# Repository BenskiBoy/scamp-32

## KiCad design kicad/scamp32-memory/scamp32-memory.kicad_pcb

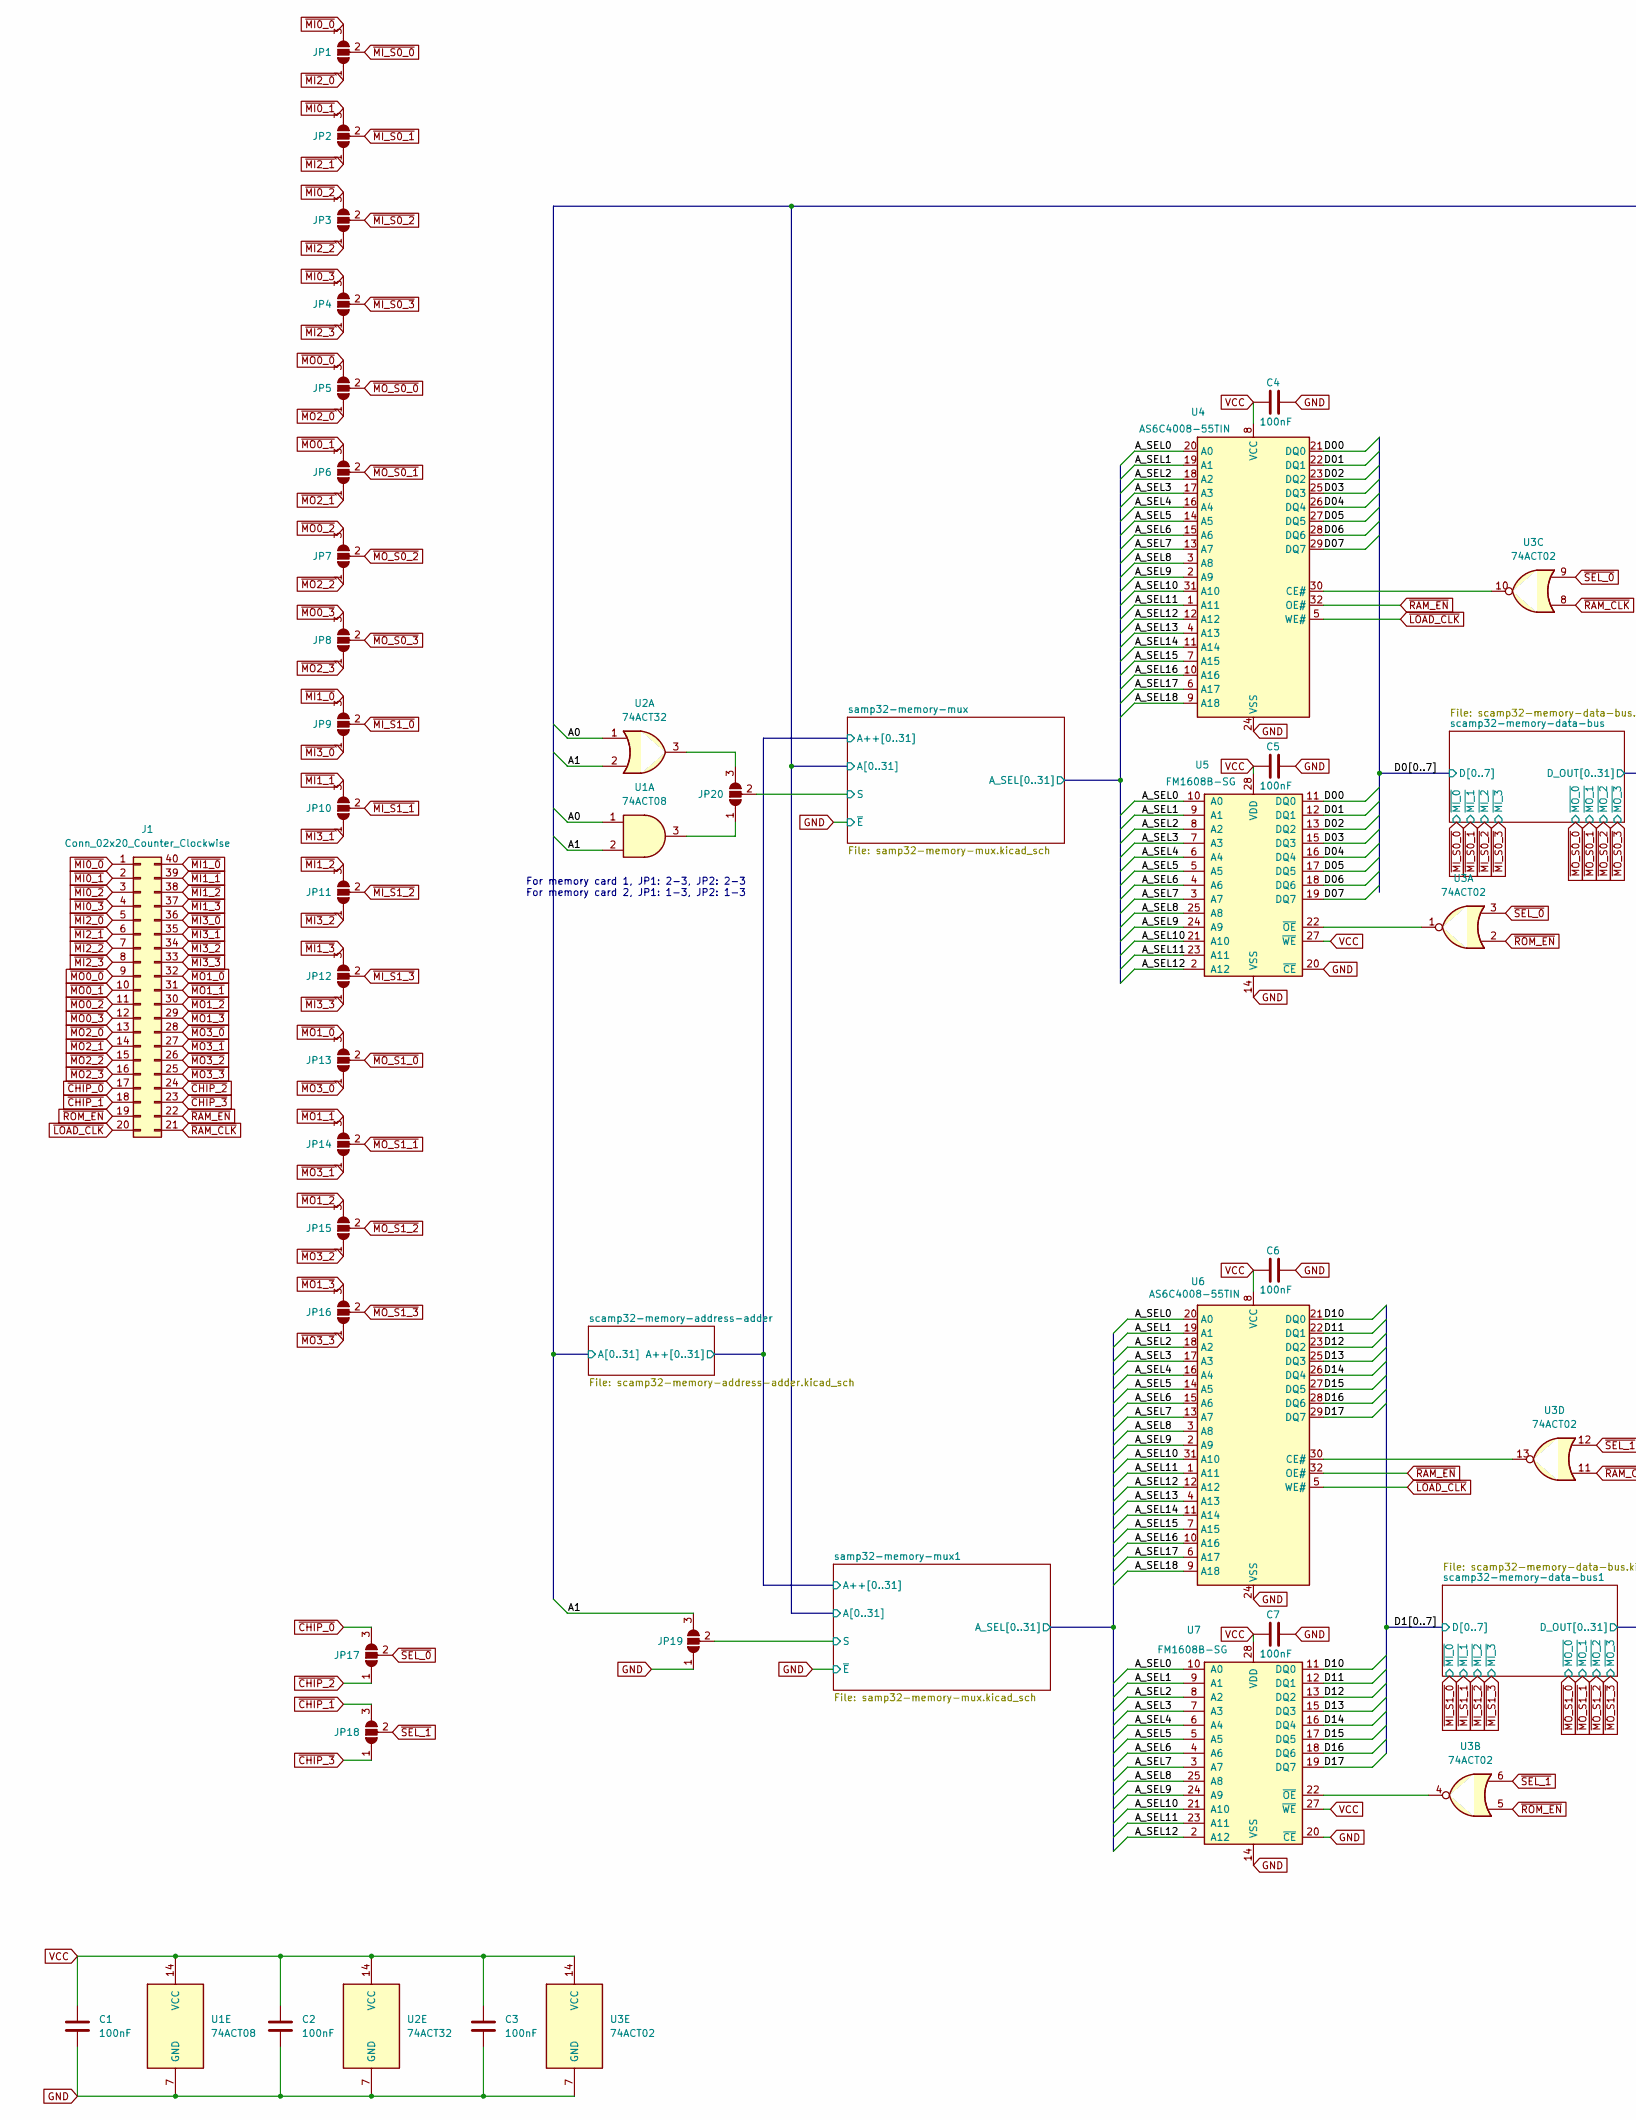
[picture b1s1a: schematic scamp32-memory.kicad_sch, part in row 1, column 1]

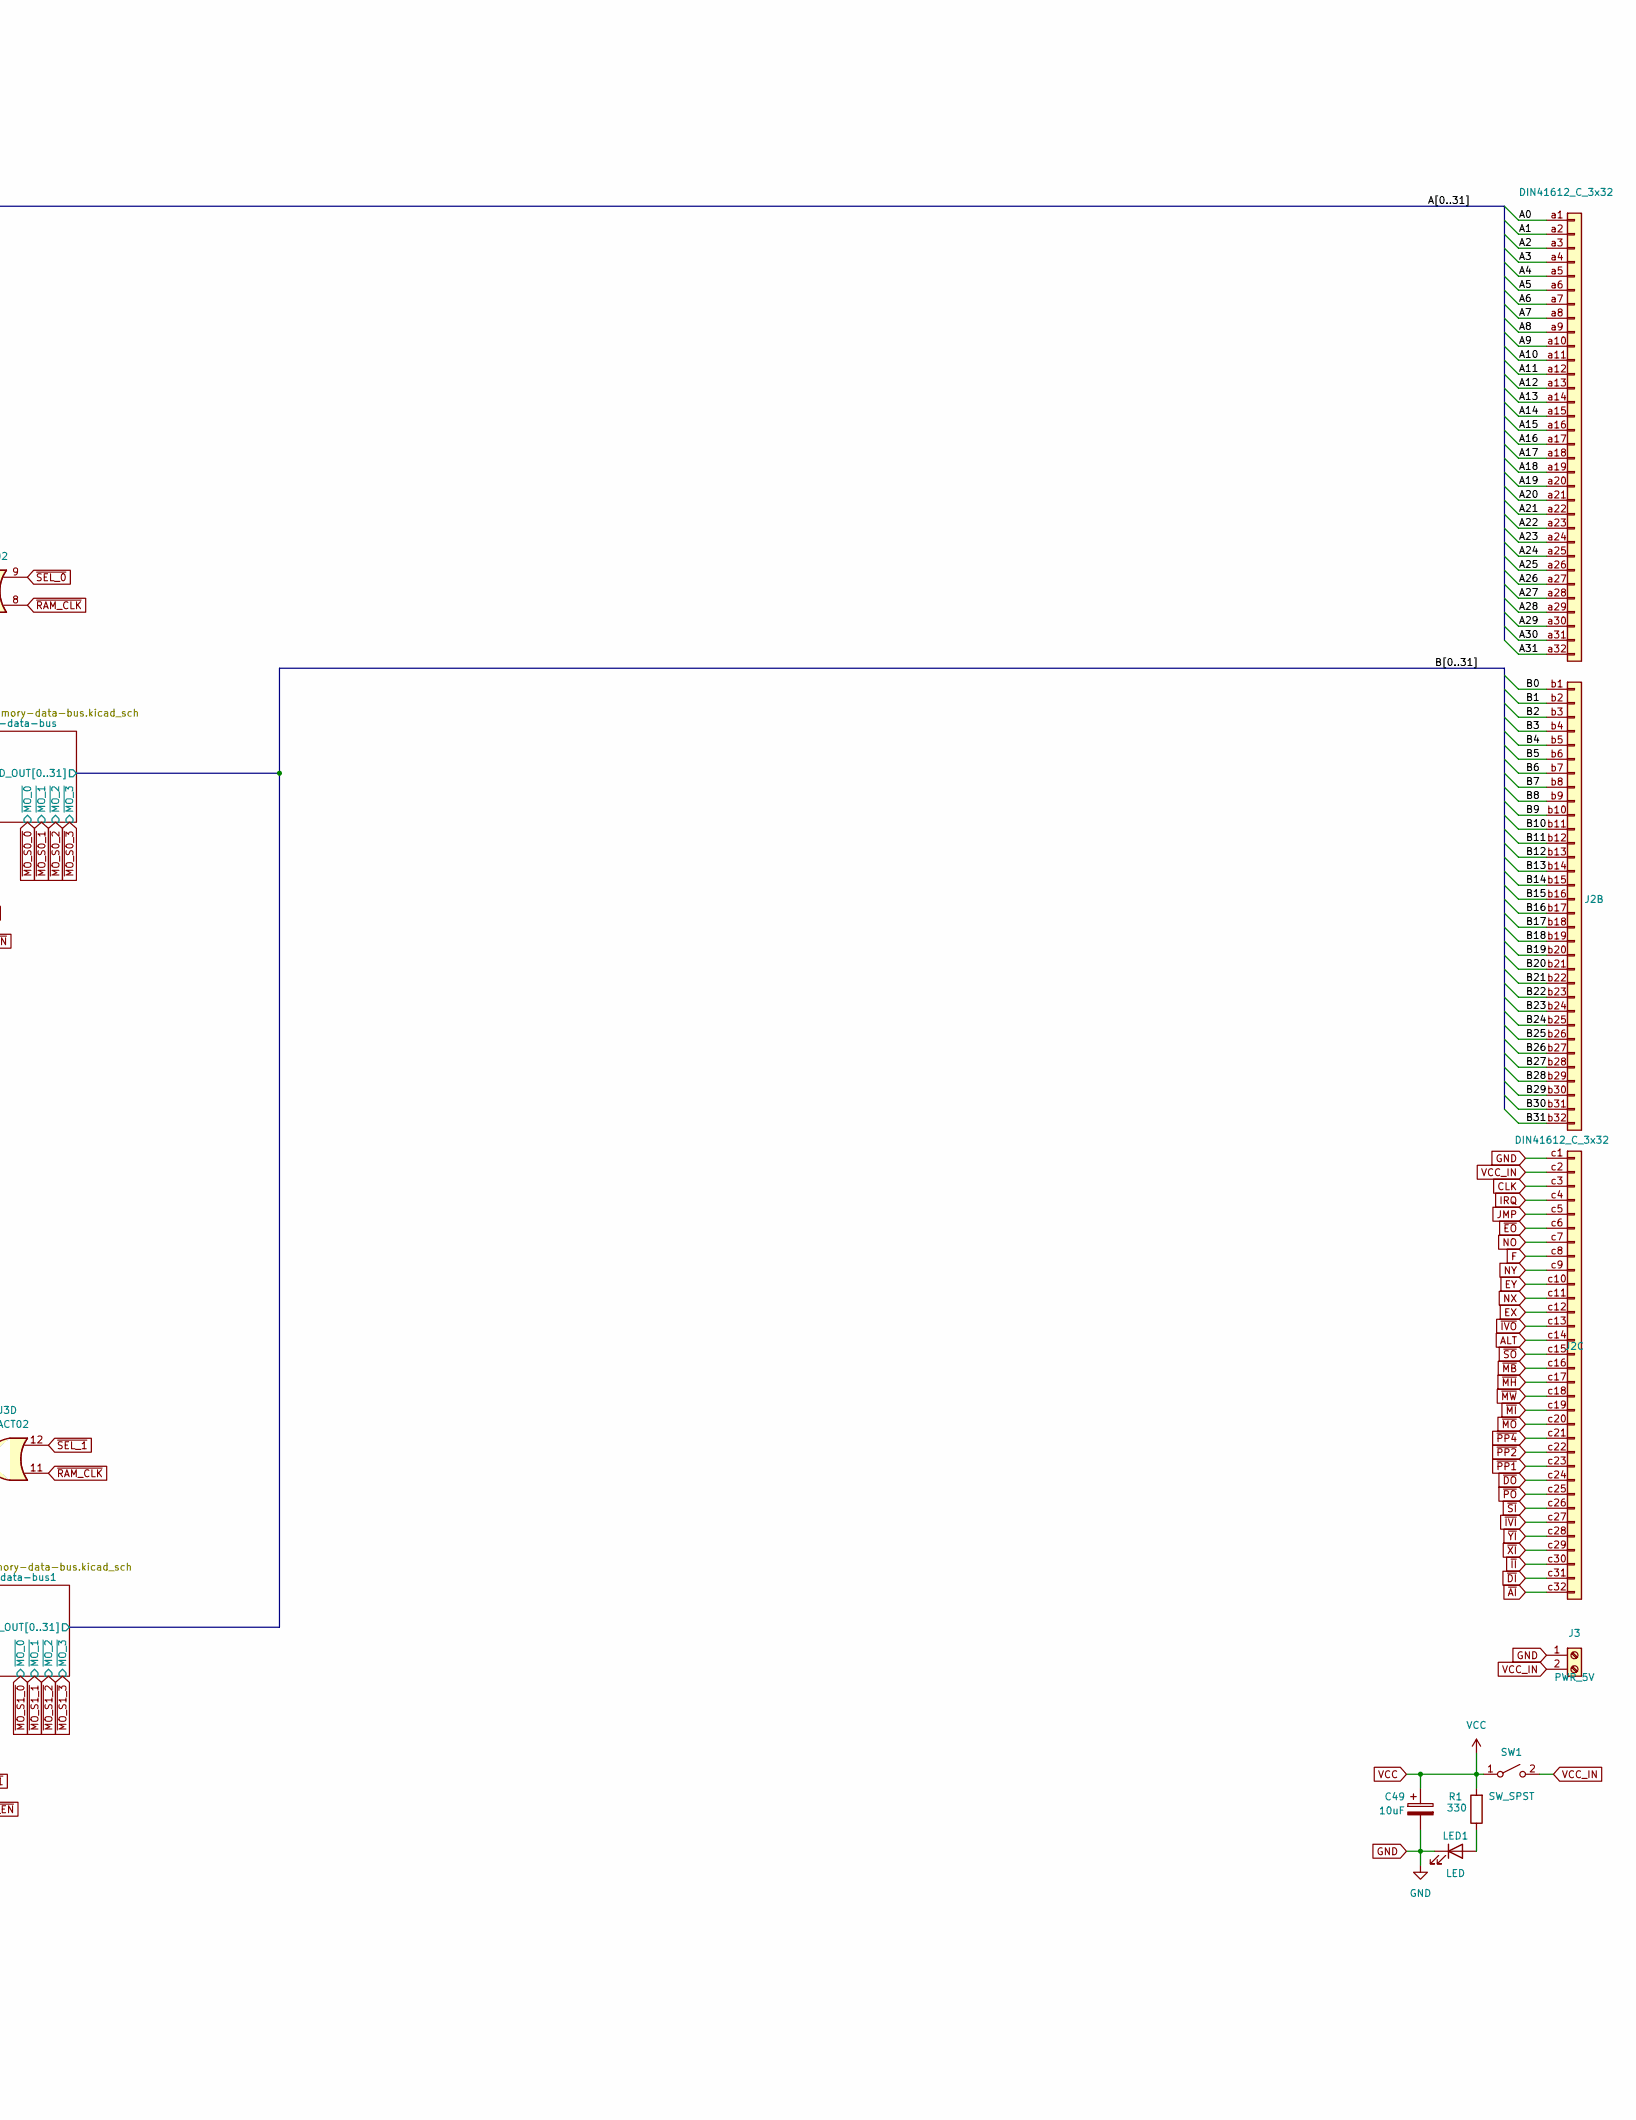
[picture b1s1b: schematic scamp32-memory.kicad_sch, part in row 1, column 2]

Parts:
C1, C2, C3, C4, C5, C6, C7: 100nF; C_0603_1608Metric
C49: 10uF; CP_Radial_D5.0mm_P2.00mm
J1: Conn_02x20_Counter_Clockwise; IDC-Header_2x20_P2.54mm_Horizontal
J2: DIN41612_C_3x32; DIN41612_C_3x32_Male_Horizontal_THT
J3: PWR_5V; TerminalBlock_Phoenix_MKDS-1,5-2-5.08_1x02_P5.08mm_Horizont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
JP1, JP2, JP3, JP4, JP5, JP6, JP7, JP8, JP9, JP10, JP11, JP12, JP13, JP14, JP15, JP16, JP17, JP18, JP19, JP20: SolderJumper_3_Open; SolderJumper-3_P1.3mm_Open_RoundedPad1.0x1.5mm_NumberLabels
LED1: LED; LED_0805_2012Metric
R1: 330; R_0805_2012Metric
SW1: SW_SPST; SW_Slide_SPDT_Straight_CK_OS102011MS2Q
U1: 74ACT08; TSSOP-14_4.4x5mm_P0.65mm
U2: 74ACT32; SOIC-14_3.9x8.7mm_P1.27mm
U3: 74ACT02; TSSOP-14_4.4x5mm_P0.65mm
U4, U6: AS6C4008-55TIN; TSOP-I-32_18.4x8mm_P0.5mm
U5, U7: FM1608B-SG; DIP_Socket-28_W11.9mm_W12.7mm_W15.24mm_W17.78mm_W18.5mm_3M_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

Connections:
/A0: J2.a1, U1.1, U2.1; also elsewhere on the board
/A1: J2.a2, JP19.3 (B), U1.2, U2.2; also elsewhere on the board
/A2: J2.a3; also elsewhere on the board
/A3: J2.a4; also elsewhere on the board
/A4: J2.a5; also elsewhere on the board
/A5: J2.a6; also elsewhere on the board
/A6: J2.a7; also elsewhere on the board
/A7: J2.a8; also elsewhere on the board
/A8: J2.a9; also elsewhere on the board
/A9: J2.a10; also elsewhere on the board
/A10: J2.a11; also elsewhere on the board
/A11: J2.a12; also elsewhere on the board
/A12: J2.a13; also elsewhere on the board
/A13: J2.a14; also elsewhere on the board
/A14: J2.a15; also elsewhere on the board
/A15: J2.a16; also elsewhere on the board
/A16: J2.a17; also elsewhere on the board
/A17: J2.a18; also elsewhere on the board
/A18: J2.a19; also elsewhere on the board
/A19: J2.a20; also elsewhere on the board
/A20: J2.a21; also elsewhere on the board
/A21: J2.a22; also elsewhere on the board
/A22: J2.a23; also elsewhere on the board
/A23: J2.a24; also elsewhere on the board
/A24: J2.a25; also elsewhere on the board
/A25: J2.a26; also elsewhere on the board
/A26: J2.a27; also elsewhere on the board
/A27: J2.a28; also elsewhere on the board
/A28: J2.a29; also elsewhere on the board
/A29: J2.a30; also elsewhere on the board
/A30: J2.a31; also elsewhere on the board
/A31: J2.a32; also elsewhere on the board
/B0: J2.b1; also elsewhere on the board
/B1: J2.b2; also elsewhere on the board
/B2: J2.b3; also elsewhere on the board
/B3: J2.b4; also elsewhere on the board
/B4: J2.b5; also elsewhere on the board
/B5: J2.b6; also elsewhere on the board
/B6: J2.b7; also elsewhere on the board
/B7: J2.b8; also elsewhere on the board
/B8: J2.b9; also elsewhere on the board
/B9: J2.b10; also elsewhere on the board
/B10: J2.b11; also elsewhere on the board
/B11: J2.b12; also elsewhere on the board
/B12: J2.b13; also elsewhere on the board
/B13: J2.b14; also elsewhere on the board
/B14: J2.b15; also elsewhere on the board
/B15: J2.b16; also elsewhere on the board
/B16: J2.b17; also elsewhere on the board
/B17: J2.b18; also elsewhere on the board
/B18: J2.b19; also elsewhere on the board
/B19: J2.b20; also elsewhere on the board
/B20: J2.b21; also elsewhere on the board
/B21: J2.b22; also elsewhere on the board
/B22: J2.b23; also elsewhere on the board
/B23: J2.b24; also elsewhere on the board
/B24: J2.b25; also elsewhere on the board
/B25: J2.b26; also elsewhere on the board
/B26: J2.b27; also elsewhere on the board
/B27: J2.b28; also elsewhere on the board
/B28: J2.b29; also elsewhere on the board
/B29: J2.b30; also elsewhere on the board
/B30: J2.b31; also elsewhere on the board
/B31: J2.b32; also elsewhere on the board
/D00: U4.21 (DQ0), U5.11 (DQ0); also elsewhere on the board
/D01: U4.22 (DQ1), U5.12 (DQ1); also elsewhere on the board
/D02: U4.23 (DQ2), U5.13 (DQ2); also elsewhere on the board
/D03: U4.25 (DQ3), U5.15 (DQ3); also elsewhere on the board
/D04: U4.26 (DQ4), U5.16 (DQ4); also elsewhere on the board
/D05: U4.27 (DQ5), U5.17 (DQ5); also elsewhere on the board
/D06: U4.28 (DQ6), U5.18 (DQ6); also elsewhere on the board
/D07: U4.29 (DQ7), U5.19 (DQ7); also elsewhere on the board
/D10: U6.21 (DQ0), U7.11 (DQ0); also elsewhere on the board
/D11: U6.22 (DQ1), U7.12 (DQ1); also elsewhere on the board
/D12: U6.23 (DQ2), U7.13 (DQ2); also elsewhere on the board
/D13: U6.25 (DQ3), U7.15 (DQ3); also elsewhere on the board
/D14: U6.26 (DQ4), U7.16 (DQ4); also elsewhere on the board
/D15: U6.27 (DQ5), U7.17 (DQ5); also elsewhere on the board
/D16: U6.28 (DQ6), U7.18 (DQ6); also elsewhere on the board
/D17: U6.29 (DQ7), U7.19 (DQ7); also elsewhere on the board
/samp32-memory-mux1/S: JP19.2 (C); also elsewhere on the board
/samp32-memory-mux/A_SEL0: U4.20 (A0), U5.10 (A0), U6.20 (A0), U7.10 (A0); also elsewhere on the board
/samp32-memory-mux/A_SEL1: U4.19 (A1), U5.9 (A1), U6.19 (A1), U7.9 (A1); also elsewhere on the board
/samp32-memory-mux/A_SEL2: U4.18 (A2), U5.8 (A2), U6.18 (A2), U7.8 (A2); also elsewhere on the board
/samp32-memory-mux/A_SEL3: U4.17 (A3), U5.7 (A3), U6.17 (A3), U7.7 (A3); also elsewhere on the board
/samp32-memory-mux/A_SEL4: U4.16 (A4), U5.6 (A4), U6.16 (A4), U7.6 (A4); also elsewhere on the board
/samp32-memory-mux/A_SEL5: U4.14 (A5), U5.5 (A5), U6.14 (A5), U7.5 (A5); also elsewhere on the board
/samp32-memory-mux/A_SEL6: U4.15 (A6), U5.4 (A6), U6.15 (A6), U7.4 (A6); also elsewhere on the board
/samp32-memory-mux/A_SEL7: U4.13 (A7), U5.3 (A7), U6.13 (A7), U7.3 (A7); also elsewhere on the board
/samp32-memory-mux/A_SEL8: U4.3 (A8), U5.25 (A8), U6.3 (A8), U7.25 (A8); also elsewhere on the board
/samp32-memory-mux/A_SEL9: U4.2 (A9), U5.24 (A9), U6.2 (A9), U7.24 (A9); also elsewhere on the board
/samp32-memory-mux/A_SEL10: U4.31 (A10), U5.21 (A10), U6.31 (A10), U7.21 (A10); also elsewhere on the board
/samp32-memory-mux/A_SEL11: U4.1 (A11), U5.23 (A11), U6.1 (A11), U7.23 (A11); also elsewhere on the board
/samp32-memory-mux/A_SEL12: U4.12 (A12), U5.2 (A12), U6.12 (A12), U7.2 (A12); also elsewhere on the board
/samp32-memory-mux/A_SEL13: U4.4 (A13), U6.4 (A13); also elsewhere on the board
/samp32-memory-mux/A_SEL14: U4.11 (A14), U6.11 (A14); also elsewhere on the board
/samp32-memory-mux/A_SEL15: U4.7 (A15), U6.7 (A15); also elsewhere on the board
/samp32-memory-mux/A_SEL16: U4.10 (A16), U6.10 (A16); also elsewhere on the board
/samp32-memory-mux/A_SEL17: U4.6 (A17), U6.6 (A17); also elsewhere on the board
/samp32-memory-mux/A_SEL18: U4.9 (A18), U6.9 (A18); also elsewhere on the board
/samp32-memory-mux/S: JP20.2 (C); also elsewhere on the board
ALT: J2.c14
CLK: J2.c3
EX: J2.c12
EY: J2.c10
F: J2.c8
GND: C1.2, C2.2, C3.2, C4.2, C5.2, C6.2, C7.2, C49.2, J2.c1, J3.1, JP19.1 (A), LED1.1 (K), U1.7 (GND), U2.7 (GND), U3.7 (GND), U4.24 (VSS), U5.14 (VSS), U5.20 (~CE), U6.24 (VSS), U7.14 (VSS), U7.20 (~CE); also elsewhere on the board
IRQ: J2.c4
JMP: J2.c5
NO: J2.c7
NX: J2.c11
NY: J2.c9
unnamed: JP20.1 (A), U1.3
unnamed: JP20.3 (B), U2.3
unnamed: LED1.2 (A), R1.1
unnamed: U3.10, U4.30 (CE#)
unnamed: U3.1, U5.22 (~OE)
unnamed: U3.13, U6.30 (CE#)
unnamed: U3.4, U7.22 (~OE)
VCC: C1.1, C2.1, C3.1, C4.1, C5.1, C6.1, C7.1, C49.1, R1.2, SW1.1 (A), U1.14 (VCC), U2.14 (VCC), U3.14 (VCC), U4.8 (VCC), U5.27 (~WE), U5.28 (VDD), U6.8 (VCC), U7.27 (~WE), U7.28 (VDD); also elsewhere on the board
VCC_IN: J2.c2, J3.2, SW1.2 (B)
~AI: J2.c32
~CHIP_0: J1.17, JP17.3 (B)
~CHIP_1: J1.18, JP18.3 (B)
~CHIP_2: J1.24, JP17.1 (A)
~CHIP_3: J1.23, JP18.1 (A)
~DI: J2.c31
~DO: J2.c24
~EO: J2.c6
~II: J2.c30
~IVI: J2.c27
~IVO: J2.c13
~LOAD_CLK: J1.20, U4.5 (WE#), U6.5 (WE#)
~MB: J2.c16
~MH: J2.c17
~MI0_0: J1.1, JP1.3 (B)
~MI0_1: J1.2, JP2.3 (B)
~MI0_2: J1.3, JP3.3 (B)
~MI0_3: J1.4, JP4.3 (B)
~MI1_0: J1.40, JP9.3 (B)
~MI1_1: J1.39, JP10.3 (B)
~MI1_2: J1.38, JP11.3 (B)
~MI1_3: J1.37, JP12.3 (B)
~MI2_0: J1.5, JP1.1 (A)
~MI2_1: J1.6, JP2.1 (A)
~MI2_2: J1.7, JP3.1 (A)
~MI2_3: J1.8, JP4.1 (A)
~MI3_0: J1.36, JP9.1 (A)
~MI3_1: J1.35, JP10.1 (A)
~MI3_2: J1.34, JP11.1 (A)
~MI3_3: J1.33, JP12.1 (A)
~MI_S0_0: JP1.2 (C); also elsewhere on the board
~MI_S0_1: JP2.2 (C); also elsewhere on the board
~MI_S0_2: JP3.2 (C); also elsewhere on the board
~MI_S0_3: JP4.2 (C); also elsewhere on the board
~MI_S1_0: JP9.2 (C); also elsewhere on the board
~MI_S1_1: JP10.2 (C); also elsewhere on the board
~MI_S1_2: JP11.2 (C); also elsewhere on the board
~MI_S1_3: JP12.2 (C); also elsewhere on the board
~MI: J2.c19
~MO0_0: J1.9, JP5.3 (B)
~MO0_1: J1.10, JP6.3 (B)
~MO0_2: J1.11, JP7.3 (B)
~MO0_3: J1.12, JP8.3 (B)
~MO1_0: J1.32, JP13.3 (B)
~MO1_1: J1.31, JP14.3 (B)
~MO1_2: J1.30, JP15.3 (B)
~MO1_3: J1.29, JP16.3 (B)
~MO2_0: J1.13, JP5.1 (A)
~MO2_1: J1.14, JP6.1 (A)
~MO2_2: J1.15, JP7.1 (A)
~MO2_3: J1.16, JP8.1 (A)
~MO3_0: J1.28, JP13.1 (A)
~MO3_1: J1.27, JP14.1 (A)
~MO3_2: J1.26, JP15.1 (A)
~MO3_3: J1.25, JP16.1 (A)
~MO_S0_0: JP5.2 (C); also elsewhere on the board
~MO_S0_1: JP6.2 (C); also elsewhere on the board
~MO_S0_2: JP7.2 (C); also elsewhere on the board
~MO_S0_3: JP8.2 (C); also elsewhere on the board
~MO_S1_0: JP13.2 (C); also elsewhere on the board
~MO_S1_1: JP14.2 (C); also elsewhere on the board
~MO_S1_2: JP15.2 (C); also elsewhere on the board
~MO_S1_3: JP16.2 (C); also elsewhere on the board
~MO: J2.c20
~MW: J2.c18
~PO: J2.c25
~PP1: J2.c23
~PP2: J2.c22
~PP4: J2.c21
~RAM_CLK: J1.21, U3.8, U3.11
~RAM_EN: J1.22, U4.32 (OE#), U6.32 (OE#)
~ROM_EN: J1.19, U3.2, U3.5
~SEL_0: JP17.2 (C), U3.3, U3.9
~SEL_1: JP18.2 (C), U3.6, U3.12
~SI: J2.c26
~SO: J2.c15
~XI: J2.c29
~YI: J2.c28

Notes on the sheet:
For memory card 1, JP1: 2-3, JP2: 2-3 For memory card 2, JP1: 1-3, JP2: 1-3

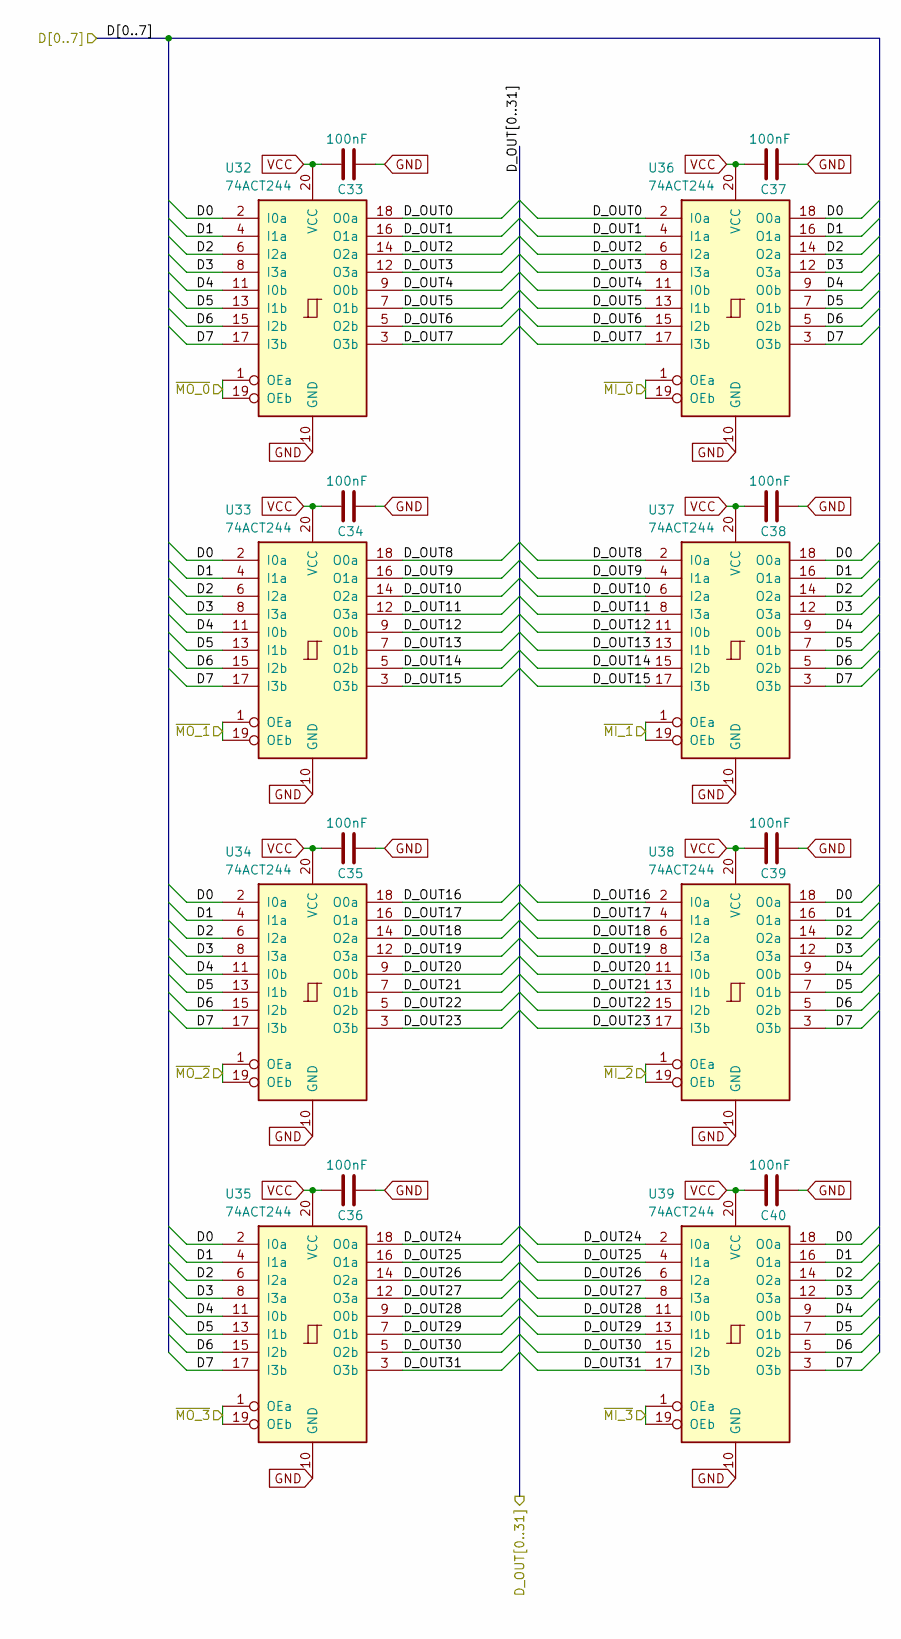
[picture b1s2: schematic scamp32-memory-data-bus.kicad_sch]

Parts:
C33, C34, C35, C36, C37, C38, C39, C40: 100nF; C_0603_1608Metric
U32, U33, U34, U35, U36, U37, U38, U39: 74ACT244; Texas_PW0020A_TSSOP-20_4.4x6.5mm_P0.65mm

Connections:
/B0: U32.18 (O0a), U36.2 (I0a); also elsewhere on the board
/B1: U32.16 (O1a), U36.4 (I1a); also elsewhere on the board
/B2: U32.14 (O2a), U36.6 (I2a); also elsewhere on the board
/B3: U32.12 (O3a), U36.8 (I3a); also elsewhere on the board
/B4: U32.9 (O0b), U36.11 (I0b); also elsewhere on the board
/B5: U32.7 (O1b), U36.13 (I1b); also elsewhere on the board
/B6: U32.5 (O2b), U36.15 (I2b); also elsewhere on the board
/B7: U32.3 (O3b), U36.17 (I3b); also elsewhere on the board
/B8: U33.18 (O0a), U37.2 (I0a); also elsewhere on the board
/B9: U33.16 (O1a), U37.4 (I1a); also elsewhere on the board
/B10: U33.14 (O2a), U37.6 (I2a); also elsewhere on the board
/B11: U33.12 (O3a), U37.8 (I3a); also elsewhere on the board
/B12: U33.9 (O0b), U37.11 (I0b); also elsewhere on the board
/B13: U33.7 (O1b), U37.13 (I1b); also elsewhere on the board
/B14: U33.5 (O2b), U37.15 (I2b); also elsewhere on the board
/B15: U33.3 (O3b), U37.17 (I3b); also elsewhere on the board
/B16: U34.18 (O0a), U38.2 (I0a); also elsewhere on the board
/B17: U34.16 (O1a), U38.4 (I1a); also elsewhere on the board
/B18: U34.14 (O2a), U38.6 (I2a); also elsewhere on the board
/B19: U34.12 (O3a), U38.8 (I3a); also elsewhere on the board
/B20: U34.9 (O0b), U38.11 (I0b); also elsewhere on the board
/B21: U34.7 (O1b), U38.13 (I1b); also elsewhere on the board
/B22: U34.5 (O2b), U38.15 (I2b); also elsewhere on the board
/B23: U34.3 (O3b), U38.17 (I3b); also elsewhere on the board
/B24: U35.18 (O0a), U39.2 (I0a); also elsewhere on the board
/B25: U35.16 (O1a), U39.4 (I1a); also elsewhere on the board
/B26: U35.14 (O2a), U39.6 (I2a); also elsewhere on the board
/B27: U35.12 (O3a), U39.8 (I3a); also elsewhere on the board
/B28: U35.9 (O0b), U39.11 (I0b); also elsewhere on the board
/B29: U35.7 (O1b), U39.13 (I1b); also elsewhere on the board
/B30: U35.5 (O2b), U39.15 (I2b); also elsewhere on the board
/B31: U35.3 (O3b), U39.17 (I3b); also elsewhere on the board
/D00: U32.2 (I0a), U33.2 (I0a), U34.2 (I0a), U35.2 (I0a), U36.18 (O0a), U37.18 (O0a), U38.18 (O0a), U39.18 (O0a); also elsewhere on the board
/D01: U32.4 (I1a), U33.4 (I1a), U34.4 (I1a), U35.4 (I1a), U36.16 (O1a), U37.16 (O1a), U38.16 (O1a), U39.16 (O1a); also elsewhere on the board
/D02: U32.6 (I2a), U33.6 (I2a), U34.6 (I2a), U35.6 (I2a), U36.14 (O2a), U37.14 (O2a), U38.14 (O2a), U39.14 (O2a); also elsewhere on the board
/D03: U32.8 (I3a), U33.8 (I3a), U34.8 (I3a), U35.8 (I3a), U36.12 (O3a), U37.12 (O3a), U38.12 (O3a), U39.12 (O3a); also elsewhere on the board
/D04: U32.11 (I0b), U33.11 (I0b), U34.11 (I0b), U35.11 (I0b), U36.9 (O0b), U37.9 (O0b), U38.9 (O0b), U39.9 (O0b); also elsewhere on the board
/D05: U32.13 (I1b), U33.13 (I1b), U34.13 (I1b), U35.13 (I1b), U36.7 (O1b), U37.7 (O1b), U38.7 (O1b), U39.7 (O1b); also elsewhere on the board
/D06: U32.15 (I2b), U33.15 (I2b), U34.15 (I2b), U35.15 (I2b), U36.5 (O2b), U37.5 (O2b), U38.5 (O2b), U39.5 (O2b); also elsewhere on the board
/D07: U32.17 (I3b), U33.17 (I3b), U34.17 (I3b), U35.17 (I3b), U36.3 (O3b), U37.3 (O3b), U38.3 (O3b), U39.3 (O3b); also elsewhere on the board
GND: C33.1, C34.1, C35.1, C36.1, C37.1, C38.1, C39.1, C40.1, U32.10 (GND), U33.10 (GND), U34.10 (GND), U35.10 (GND), U36.10 (GND), U37.10 (GND), U38.10 (GND), U39.10 (GND); also elsewhere on the board
VCC: C33.2, C34.2, C35.2, C36.2, C37.2, C38.2, C39.2, C40.2, U32.20 (VCC), U33.20 (VCC), U34.20 (VCC), U35.20 (VCC), U36.20 (VCC), U37.20 (VCC), U38.20 (VCC), U39.20 (VCC); also elsewhere on the board
~MI_S0_0: U36.1 (OEa), U36.19 (OEb); also elsewhere on the board
~MI_S0_1: U37.1 (OEa), U37.19 (OEb); also elsewhere on the board
~MI_S0_2: U38.1 (OEa), U38.19 (OEb); also elsewhere on the board
~MI_S0_3: U39.1 (OEa), U39.19 (OEb); also elsewhere on the board
~MO_S0_0: U32.1 (OEa), U32.19 (OEb); also elsewhere on the board
~MO_S0_1: U33.1 (OEa), U33.19 (OEb); also elsewhere on the board
~MO_S0_2: U34.1 (OEa), U34.19 (OEb); also elsewhere on the board
~MO_S0_3: U35.1 (OEa), U35.19 (OEb); also elsewhere on the board

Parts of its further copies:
C41, C42, C43, C44, C45, C46, C47, C48: 100nF; C_0603_1608Metric
U40, U41, U42, U43, U44, U45, U46, U47: 74ACT244; Texas_PW0020A_TSSOP-20_4.4x6.5mm_P0.65mm

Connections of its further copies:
/B0: U40.18 (O0a), U44.2 (I0a); also elsewhere on the board
/B1: U40.16 (O1a), U44.4 (I1a); also elsewhere on the board
/B2: U40.14 (O2a), U44.6 (I2a); also elsewhere on the board
/B3: U40.12 (O3a), U44.8 (I3a); also elsewhere on the board
/B4: U40.9 (O0b), U44.11 (I0b); also elsewhere on the board
/B5: U40.7 (O1b), U44.13 (I1b); also elsewhere on the board
/B6: U40.5 (O2b), U44.15 (I2b); also elsewhere on the board
/B7: U40.3 (O3b), U44.17 (I3b); also elsewhere on the board
/B8: U41.18 (O0a), U45.2 (I0a); also elsewhere on the board
/B9: U41.16 (O1a), U45.4 (I1a); also elsewhere on the board
/B10: U41.14 (O2a), U45.6 (I2a); also elsewhere on the board
/B11: U41.12 (O3a), U45.8 (I3a); also elsewhere on the board
/B12: U41.9 (O0b), U45.11 (I0b); also elsewhere on the board
/B13: U41.7 (O1b), U45.13 (I1b); also elsewhere on the board
/B14: U41.5 (O2b), U45.15 (I2b); also elsewhere on the board
/B15: U41.3 (O3b), U45.17 (I3b); also elsewhere on the board
/B16: U42.18 (O0a), U46.2 (I0a); also elsewhere on the board
/B17: U42.16 (O1a), U46.4 (I1a); also elsewhere on the board
/B18: U42.14 (O2a), U46.6 (I2a); also elsewhere on the board
/B19: U42.12 (O3a), U46.8 (I3a); also elsewhere on the board
/B20: U42.9 (O0b), U46.11 (I0b); also elsewhere on the board
/B21: U42.7 (O1b), U46.13 (I1b); also elsewhere on the board
/B22: U42.5 (O2b), U46.15 (I2b); also elsewhere on the board
/B23: U42.3 (O3b), U46.17 (I3b); also elsewhere on the board
/B24: U43.18 (O0a), U47.2 (I0a); also elsewhere on the board
/B25: U43.16 (O1a), U47.4 (I1a); also elsewhere on the board
/B26: U43.14 (O2a), U47.6 (I2a); also elsewhere on the board
/B27: U43.12 (O3a), U47.8 (I3a); also elsewhere on the board
/B28: U43.9 (O0b), U47.11 (I0b); also elsewhere on the board
/B29: U43.7 (O1b), U47.13 (I1b); also elsewhere on the board
/B30: U43.5 (O2b), U47.15 (I2b); also elsewhere on the board
/B31: U43.3 (O3b), U47.17 (I3b); also elsewhere on the board
/D10: U40.2 (I0a), U41.2 (I0a), U42.2 (I0a), U43.2 (I0a), U44.18 (O0a), U45.18 (O0a), U46.18 (O0a), U47.18 (O0a); also elsewhere on the board
/D11: U40.4 (I1a), U41.4 (I1a), U42.4 (I1a), U43.4 (I1a), U44.16 (O1a), U45.16 (O1a), U46.16 (O1a), U47.16 (O1a); also elsewhere on the board
/D12: U40.6 (I2a), U41.6 (I2a), U42.6 (I2a), U43.6 (I2a), U44.14 (O2a), U45.14 (O2a), U46.14 (O2a), U47.14 (O2a); also elsewhere on the board
/D13: U40.8 (I3a), U41.8 (I3a), U42.8 (I3a), U43.8 (I3a), U44.12 (O3a), U45.12 (O3a), U46.12 (O3a), U47.12 (O3a); also elsewhere on the board
/D14: U40.11 (I0b), U41.11 (I0b), U42.11 (I0b), U43.11 (I0b), U44.9 (O0b), U45.9 (O0b), U46.9 (O0b), U47.9 (O0b); also elsewhere on the board
/D15: U40.13 (I1b), U41.13 (I1b), U42.13 (I1b), U43.13 (I1b), U44.7 (O1b), U45.7 (O1b), U46.7 (O1b), U47.7 (O1b); also elsewhere on the board
/D16: U40.15 (I2b), U41.15 (I2b), U42.15 (I2b), U43.15 (I2b), U44.5 (O2b), U45.5 (O2b), U46.5 (O2b), U47.5 (O2b); also elsewhere on the board
/D17: U40.17 (I3b), U41.17 (I3b), U42.17 (I3b), U43.17 (I3b), U44.3 (O3b), U45.3 (O3b), U46.3 (O3b), U47.3 (O3b); also elsewhere on the board
GND: C41.1, C42.1, C43.1, C44.1, C45.1, C46.1, C47.1, C48.1, U40.10 (GND), U41.10 (GND), U42.10 (GND), U43.10 (GND), U44.10 (GND), U45.10 (GND), U46.10 (GND), U47.10 (GND); also elsewhere on the board
VCC: C41.2, C42.2, C43.2, C44.2, C45.2, C46.2, C47.2, C48.2, U40.20 (VCC), U41.20 (VCC), U42.20 (VCC), U43.20 (VCC), U44.20 (VCC), U45.20 (VCC), U46.20 (VCC), U47.20 (VCC); also elsewhere on the board
~MI_S1_0: U44.1 (OEa), U44.19 (OEb); also elsewhere on the board
~MI_S1_1: U45.1 (OEa), U45.19 (OEb); also elsewhere on the board
~MI_S1_2: U46.1 (OEa), U46.19 (OEb); also elsewhere on the board
~MI_S1_3: U47.1 (OEa), U47.19 (OEb); also elsewhere on the board
~MO_S1_0: U40.1 (OEa), U40.19 (OEb); also elsewhere on the board
~MO_S1_1: U41.1 (OEa), U41.19 (OEb); also elsewhere on the board
~MO_S1_2: U42.1 (OEa), U42.19 (OEb); also elsewhere on the board
~MO_S1_3: U43.1 (OEa), U43.19 (OEb); also elsewhere on the board
